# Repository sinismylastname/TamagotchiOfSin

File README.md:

# TamagotchiOfSin
A beginner tamagotchi project

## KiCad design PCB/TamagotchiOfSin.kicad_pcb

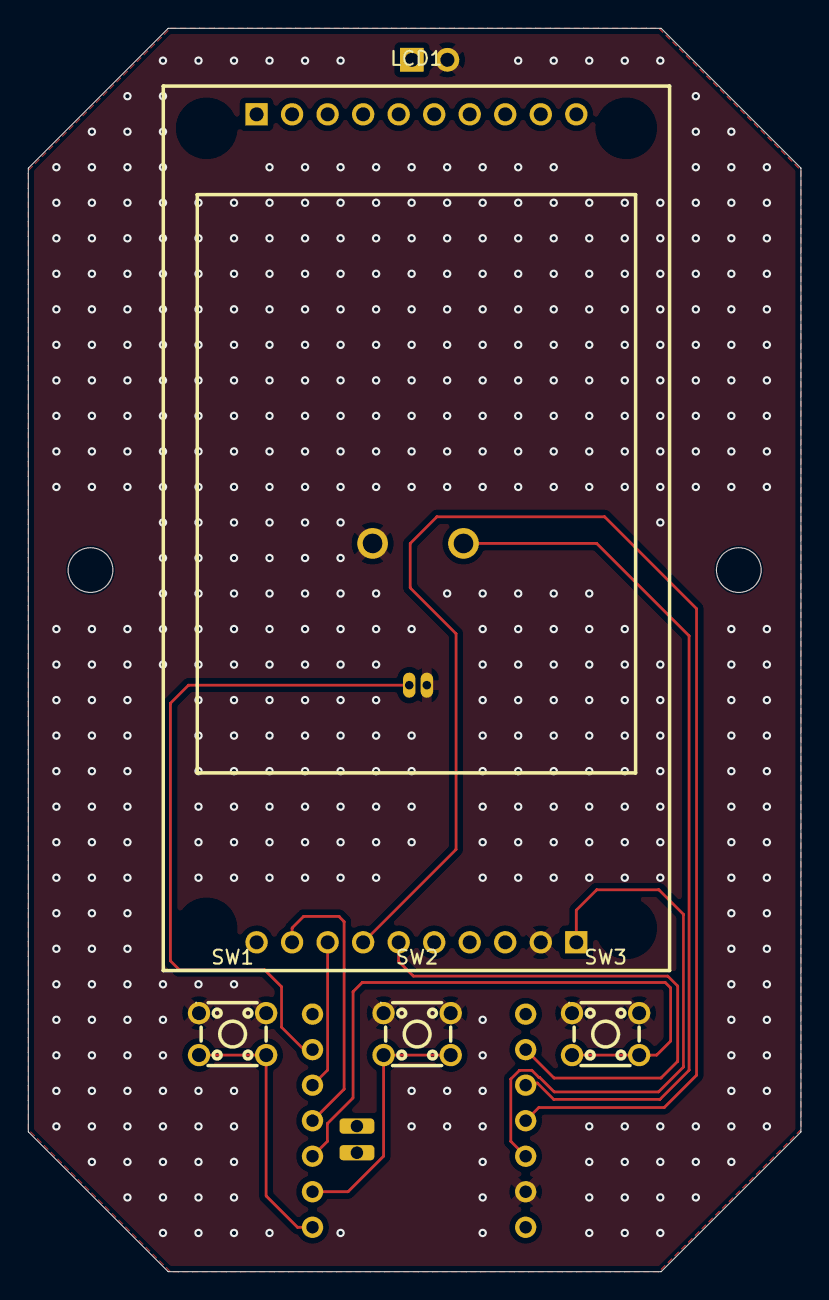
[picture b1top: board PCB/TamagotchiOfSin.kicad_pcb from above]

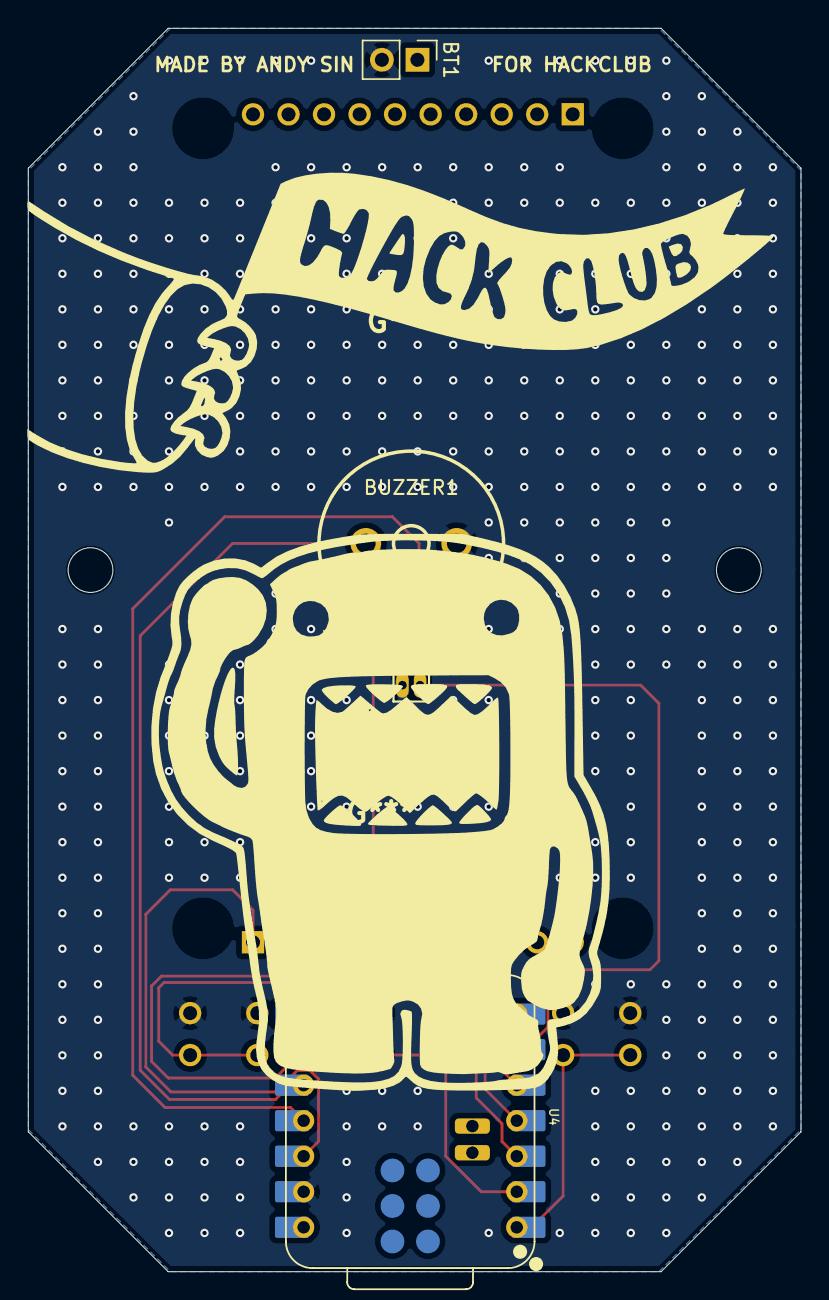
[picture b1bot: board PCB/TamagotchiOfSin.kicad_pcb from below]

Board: 2 copper layers, 55.2 x 88.9 mm, 8 parts (4 on the bottom side), 11 nets.

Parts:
BT1: Battery_Cell; PinHeader_1x02_P2.54mm_Vertical
BUZZER1: 1207-P6.5MM; BUZ-TH_BD12.5-P6.50-D1.4
LCD1: HS20S010B; LCD-TH_HS20S010B
MOT1: LCM1027A2445F; VIBRATING-MOTOR-SMD_WELDING
SW1, SW2, SW3: SW_Push; SW-TH_4P-L4.5-W4.5-P3.00-LS4.8
U4: XIAO-ESP32-C3-SMD; XIAO-ESP32-C3-DIP-SMD

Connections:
+3V3: LCD1.11 (VCC), U4.12 (3V3)
GND: BT1.2 (-), BUZZER1.2 (-), LCD1.12 (GND), MOT1.1 (-), SW1.1, SW2.1, SW3.1, U4.13 (GND)
unnamed: BUZZER1.1 (+), U4.10 (GPIO9_D9_MISO)
unnamed: MOT1.2 (+), U4.6 (GPIO7_D5_SCL)
unnamed: SW1.2, U4.1 (GPIO2_A0_D0)
unnamed: SW2.2, U4.2 (GPIO3_A1_D1)
unnamed: SW3.2, U4.3 (GPIO4_A2_D2)
unnamed: LCD1.19 (RES), U4.4 (GPIO5_A3_D3)
unnamed: LCD1.18 (DC), U4.5 (GPIO6_D4_SDA)
unnamed: LCD1.16 (CLK), U4.9 (GPIO8_D8_SCK)
unnamed: LCD1.17 (SDA), U4.11 (GPIO10_D10_MOSI)

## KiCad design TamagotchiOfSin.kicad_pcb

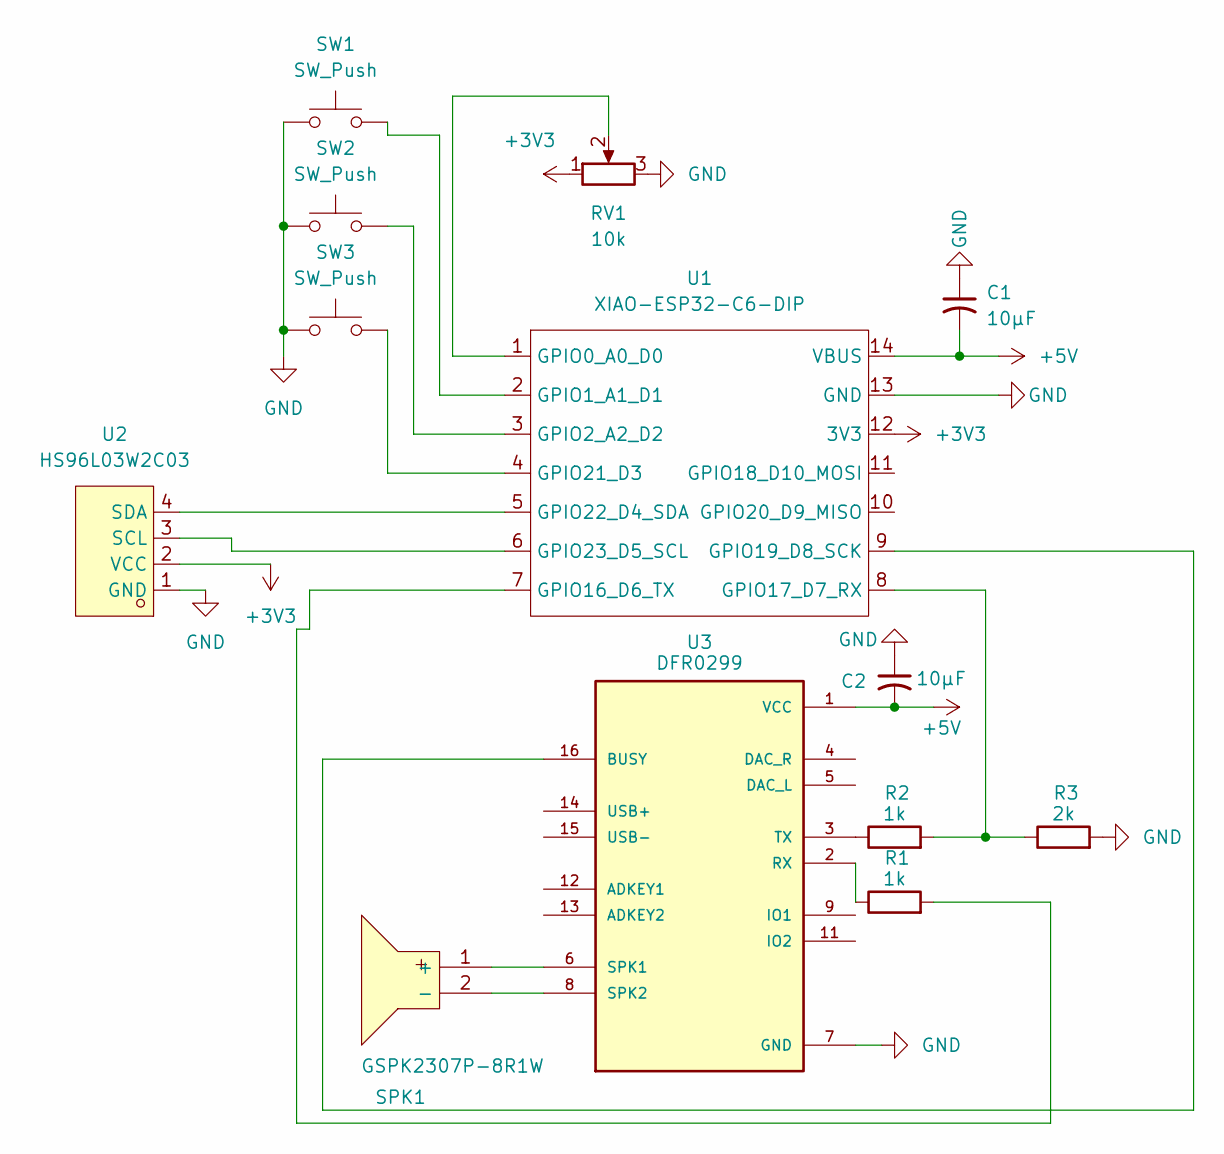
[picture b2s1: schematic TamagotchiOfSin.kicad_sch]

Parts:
C1, C2: 10µF; C0402
R1, R2: 1k; RES-TH_BD2.7-L6.2-P10.20-D0.4
R3: 2k; RES-TH_BD2.3-L6.5-P10.50-D0.5
RV1: 10k; RES-ADJ-TH_RK09D1130C3C
SPK1: GSPK2307P-8R1W; SPK-TH_BD23.0-P10.00-D0.8-L-RD; MPN GSPK2307P-8R1W; LCSC Part C530531
SW1, SW2, SW3: SW_Push; SW-TH_4P-L4.5-W4.5-P3.00-LS4.8
U1: XIAO-ESP32-C6-DIP; XIAO-ESP32-C6-SMD
U2: HS96L03W2C03; OLED-TH_L27.8-W27.2-P2.54_C9900033791; MPN HS96L03W2C03; LCSC Part C5248080
U3: DFR0299; MODULE_DFR0299; DigiKey_Part_Number 1738-1041-ND

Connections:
+3V3: RV1.1, U1.12 (3V3), U2.2 (VCC)
+5V: C1.2, C2.2, U1.14 (VBUS), U3.1 (VCC)
GND: C1.1, C2.1, R3.2, RV1.3, SW1.1, SW2.1, SW3.1, U1.13 (GND), U2.1 (GND), U3.7 (GND), U3.10 (GND)
unnamed: SPK1.1 (+), U3.6 (SPK1)
unnamed: SPK1.2 (-), U3.8 (SPK2)
unnamed: RV1.2, U1.1 (GPIO0_A0_D0)
unnamed: SW1.2, U1.2 (GPIO1_A1_D1)
unnamed: SW2.2, U1.3 (GPIO2_A2_D2)
unnamed: R1.2, U1.7 (GPIO16_D6_TX)
unnamed: R2.2, R3.1, U1.8 (GPIO17_D7_RX)
unnamed: U1.9 (GPIO19_D8_SCK), U3.16 (BUSY)
unnamed: SW3.2, U1.4 (GPIO21_D3)
unnamed: U1.5 (GPIO22_D4_SDA), U2.4 (SDA)
unnamed: U1.6 (GPIO23_D5_SCL), U2.3 (SCL)
unnamed: R1.1, U3.2 (RX)
unnamed: R2.1, U3.3 (TX)

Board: 2 copper layers, 13 parts (0 on the bottom side), 16 nets, no tracks yet.

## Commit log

2026-04-22 finished pcb
2026-04-22 added 3d pic
2026-04-23 i did NOT finish that pcb. noticed like 50 million issues... RESOLVEDgit add .git add .
2026-04-23 some cad files, gerber was somehow zipped wrong...?????????? fixed stuff, placeholder code file
2026-05-06 updated cad, pcb, not code yet
